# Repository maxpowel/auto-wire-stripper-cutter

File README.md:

# Automatic Wire Stripper and Cutter

A 3D printed automatic wire stripper and cutter. You simply choose your measurements on a screen, press a button, and it does it all for you. It will strip the wire and cut the wire depending on the options you chose.

You can see it in action! [video](https://youtu.be/TFqQvDHJAgU)

Check the original repo for extra details, I highly recommend it!

# Changes provided by this fork

The origingal project is awesome but I need more accuracy and control because my cables are thinner (like 1.1mm diameter) and weaker. I have a lot of experience with `Trinamic` drivers and I thought that I can make the machine
fit to my case using TMC2209 instead of generic ones.

The benefits I got when changing from generic drives to TMC2209 are:
 * Far more accuracy. With the microstepping feature I can achieve near absolute precission.
 * Autocalibration: The TMC2209 has stallGuard so you can detect when the motor is doing more force so we
 can detect when the blade reached the cable so we dont have to manually masure an calibrate. It is also 
 allows us to detect when the cut is done.
 * Silence: With StealthChop the motors are inaudible and the accuracy is still great. Anyway this is optional.
 * Control: Using UART protocol you can control the max current and much more parameters easily.
 * The motor movement is very smooth

I also changed the library `Stepper` by `AccelStepper`. The reason is that AccelStepper does not block so is easier
to control at every step if everything is going fine. It also handles accelerations easily so the cuts are less
aggresive with the cable.

The project is migrated from `Arduino IDE` to `platformio`. The platformio project
 is the `AutoWireCutterStripper`folder

I also changed the encoder library to support generic EC11 encoders. I was not able to make it works with the original
library. Also, the encoder change detection is done using interrupts instead of polling so we have more cpu cycles
 (the esp32 can use any gpio as interrupt so there is no reason for not using it) and smoother detection.

The code was mostly refactorized to make it easier to extend and more organized. The code is now splitted into
three main parts:
 * Guillotine: A class to control the machine intself. The blades, movement, retraction... An easy to use driver class.
 * UI: All related to the UI. The buttons, display and encoder.
 * WebUi: Connect it to wifi and control the machine with your computer

The idea was to decouple the functionality from the UI. So now you could be able to control the blades using other
user interfaces like a web hosted in the `ESP32`. Or using other kind of screens or buttons.

The last thing I did is a printable base to attach all the parts (base.stl and the openscad base.scad). It costs like 100g of material but for me it worth it.

# Wifi UI

It is just a simple web page to control the machine

You can control the machine specifying milimeters or steps. It is very useful for the calibration process.
Then the cable configuration like the one displayed in the oled screen and finally an extra option to control
the threshold of the StallGuard (in case you want auto homing). Homing the the proccess to go a known neutral
position (like in 3D printing).

The application is done using angular under the directory "dashboard"

# PCB Board

The design is not very complex but you have to solder so many cables. I made
my first hand made board and once everything was fine I designed a board using
`Kicad`. The gerbers are ready to be used with any PCB manufacturer at [kicad-wire-cutter/gerbers.zip](kicad-wire-cutter/gerbers.zip) but I also
provide the kicad files so you can edit it and adapt it to your own needs.

This is the real PCB

And the PCB with the elements soldered

It provides an extra power connector in case you prefer to use this
kind.

My old board just for reference. It took a lot of time and care to build it.
We all remember it forever but it is not needed anymore. Thank you for
 your service little board.

This is how it looks in the case

# State Machine

The cutting process is managed by a state machine. I think that it makes the
process easier to understand, easier to modify and robust. This is the diagram
of the state machine

It is very simple and apart form the variable `totalStrips` is just need
to know the previous state.

# Images of the machine I built

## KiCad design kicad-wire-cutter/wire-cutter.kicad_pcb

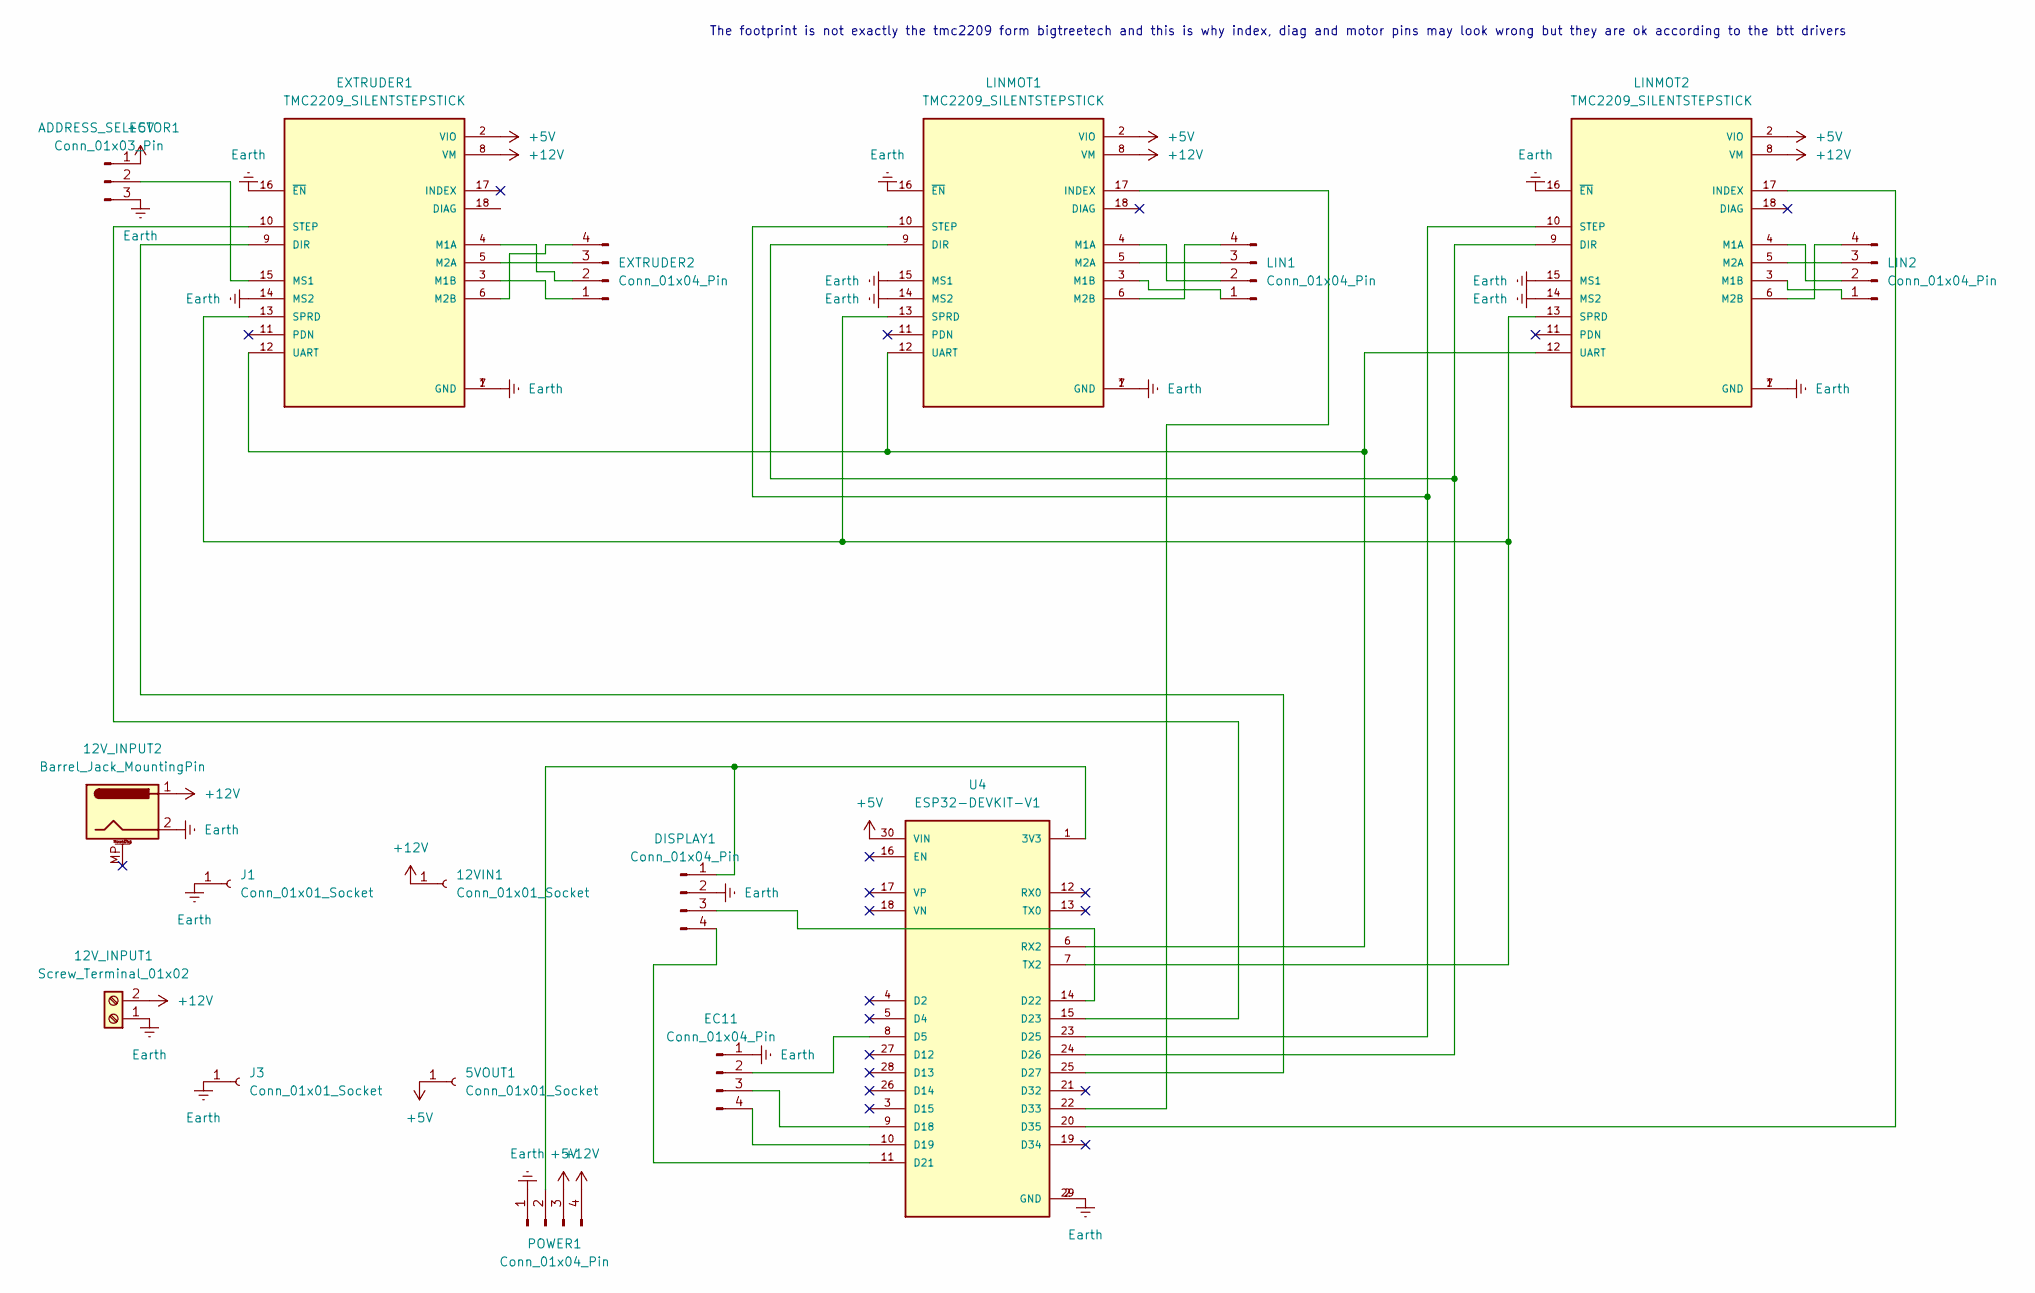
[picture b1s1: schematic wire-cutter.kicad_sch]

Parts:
5VOUT1, 12VIN1: Conn_01x01_Socket; PinHeader_1x01_P2.54mm_Vertical
12V_INPUT1: Screw_Terminal_01x02; TerminalBlock_bornier-2_P5.08mm
12V_INPUT2: Barrel_Jack_MountingPin; BarrelJack_Horizontal
ADDRESS_SELECTOR1: Conn_01x03_Pin; PinHeader_1x03_P2.54mm_Vertical
DISPLAY1: Conn_01x04_Pin; PinHeader_1x04_P2.54mm_Vertical
EC11: Conn_01x04_Pin; PinHeader_1x04_P2.54mm_Vertical
EXTRUDER1: TMC2209_SILENTSTEPSTICK; MODULE_TMC2209_SILENTSTEPSTICK; PARTREV 1.20
EXTRUDER2: Conn_01x04_Pin; PinSocket_1x04_P2.54mm_Vertical
J1, J3: Conn_01x01_Socket; PinHeader_1x01_P2.54mm_Vertical
LIN1, LIN2: Conn_01x04_Pin; PinSocket_1x04_P2.54mm_Vertical
LINMOT1, LINMOT2: TMC2209_SILENTSTEPSTICK; MODULE_TMC2209_SILENTSTEPSTICK; PARTREV 1.20
POWER1: Conn_01x04_Pin; PinHeader_1x04_P2.54mm_Vertical
U4: ESP32-DEVKIT-V1; MODULE_ESP32_DEVKIT_V1; PARTREV N/A

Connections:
+5V: 5VOUT1.1, ADDRESS_SELECTOR1.1, EXTRUDER1.2 (VIO), LINMOT1.2 (VIO), LINMOT2.2 (VIO), POWER1.3, U4.30 (VIN)
+12V: 12VIN1.1, 12V_INPUT1.2, 12V_INPUT2.1, EXTRUDER1.8 (VM), LINMOT1.8 (VM), LINMOT2.8 (VM), POWER1.4
Earth: 12V_INPUT1.1, 12V_INPUT2.2, ADDRESS_SELECTOR1.3, DISPLAY1.2, EC11.1, EXTRUDER1.1 (GND), EXTRUDER1.7 (GND), EXTRUDER1.14 (MS2), EXTRUDER1.16 (~EN), J1.1, J3.1, LINMOT1.1 (GND), LINMOT1.7 (GND), LINMOT1.14 (MS2), LINMOT1.15 (MS1), LINMOT1.16 (~EN), LINMOT2.1 (GND), LINMOT2.7 (GND), LINMOT2.14 (MS2), LINMOT2.15 (MS1), LINMOT2.16 (~EN), POWER1.1, U4.2 (GND), U4.29 (GND)
unnamed: ADDRESS_SELECTOR1.2, EXTRUDER1.15 (MS1)
unnamed: DISPLAY1.1, POWER1.2, U4.1 (3V3)
unnamed: DISPLAY1.3, U4.14 (D22)
unnamed: DISPLAY1.4, U4.11 (D21)
unnamed: EC11.2, U4.8 (D5)
unnamed: EC11.3, U4.9 (D18)
unnamed: EC11.4, U4.10 (D19)
unnamed: EXTRUDER1.9 (DIR), U4.25 (D27)
unnamed: EXTRUDER1.4 (M1A), EXTRUDER2.2
unnamed: EXTRUDER1.3 (M1B), EXTRUDER2.1
unnamed: EXTRUDER1.5 (M2A), EXTRUDER2.3
unnamed: EXTRUDER1.6 (M2B), EXTRUDER2.4
unnamed: EXTRUDER1.13 (SPRD), LINMOT1.13 (SPRD), LINMOT2.13 (SPRD), U4.7 (TX2)
unnamed: EXTRUDER1.10 (STEP), U4.15 (D23)
unnamed: EXTRUDER1.12 (UART), LINMOT1.12 (UART), LINMOT2.12 (UART), U4.6 (RX2)
unnamed: LIN1.1, LINMOT1.3 (M1B)
unnamed: LIN1.2, LINMOT1.4 (M1A)
unnamed: LIN1.3, LINMOT1.5 (M2A)
unnamed: LIN1.4, LINMOT1.6 (M2B)
unnamed: LIN2.1, LINMOT2.3 (M1B)
unnamed: LIN2.2, LINMOT2.4 (M1A)
unnamed: LIN2.3, LINMOT2.5 (M2A)
unnamed: LIN2.4, LINMOT2.6 (M2B)
unnamed: LINMOT1.9 (DIR), LINMOT2.9 (DIR), U4.24 (D26)
unnamed: LINMOT1.17 (INDEX), U4.22 (D33)
unnamed: LINMOT1.10 (STEP), LINMOT2.10 (STEP), U4.23 (D25)
unnamed: LINMOT2.17 (INDEX), U4.20 (D35)

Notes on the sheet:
The footprint is not exactly the tmc2209 form bigtreetech and this is why index, diag and motor pins may look wrong but they are ok according to the btt drivers

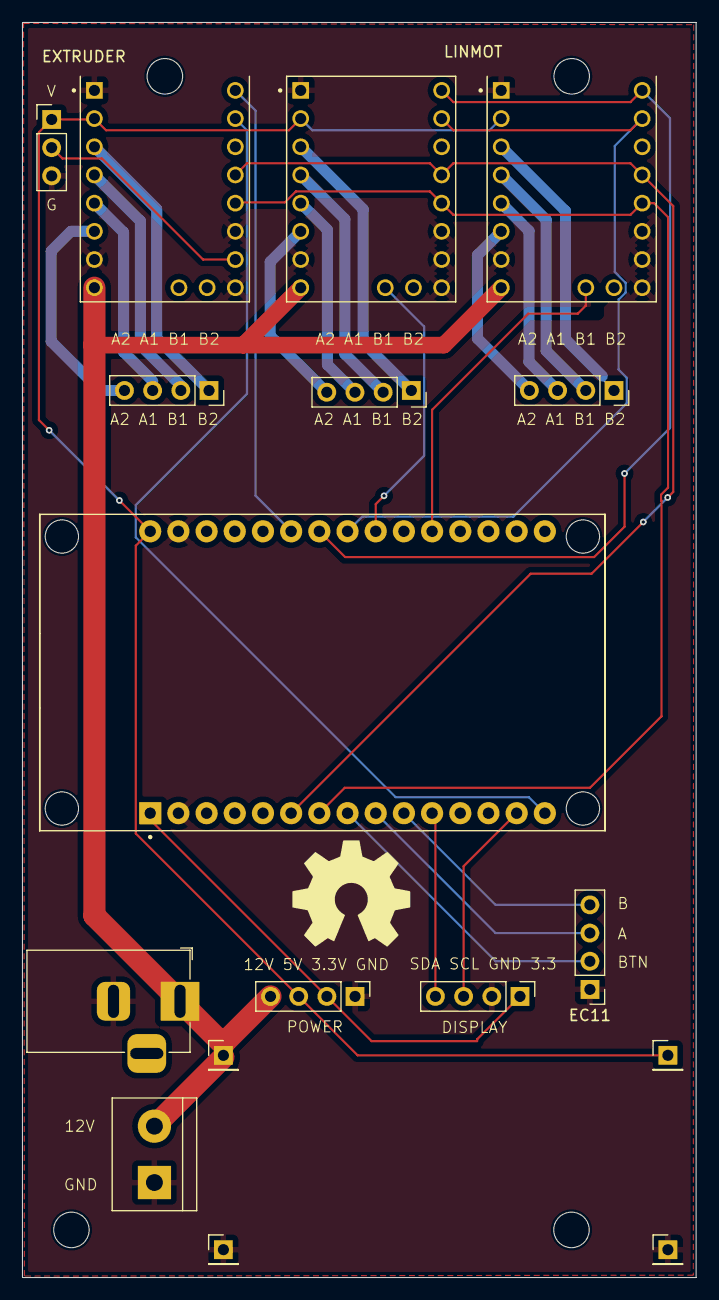
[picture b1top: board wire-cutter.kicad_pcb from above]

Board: 2 copper layers, 60.7 x 113.1 mm, 17 parts (0 on the bottom side), 30 nets.

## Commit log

2022-03-04 Add license.
2022-03-04 Update readme, add Arduino sketch.
2022-03-04 Add 3D models.
2022-05-11 Add links to components.
2022-05-23 Add assembly layout.
2022-07-25 Add oled display i2c address note
2022-08-01 Add note for ESP32 boot button on upload
2022-09-26 Add board size to assembly layout pdf
2022-09-26 Add gitignore and auto format arduino sketch
2022-09-26 Fix encoder interrupt issue
2022-11-24 Add stl 3d models.
2023-04-16 Add assembly model design file.
2024-09-27 Added initial version
2024-09-30 Added state machine
2024-10-01 Added PCB files and improved README
2024-10-17 Added PCB images
2024-10-22 Finished full cut process
2024-10-24 Added wifi stuff
2024-10-24 Added config
